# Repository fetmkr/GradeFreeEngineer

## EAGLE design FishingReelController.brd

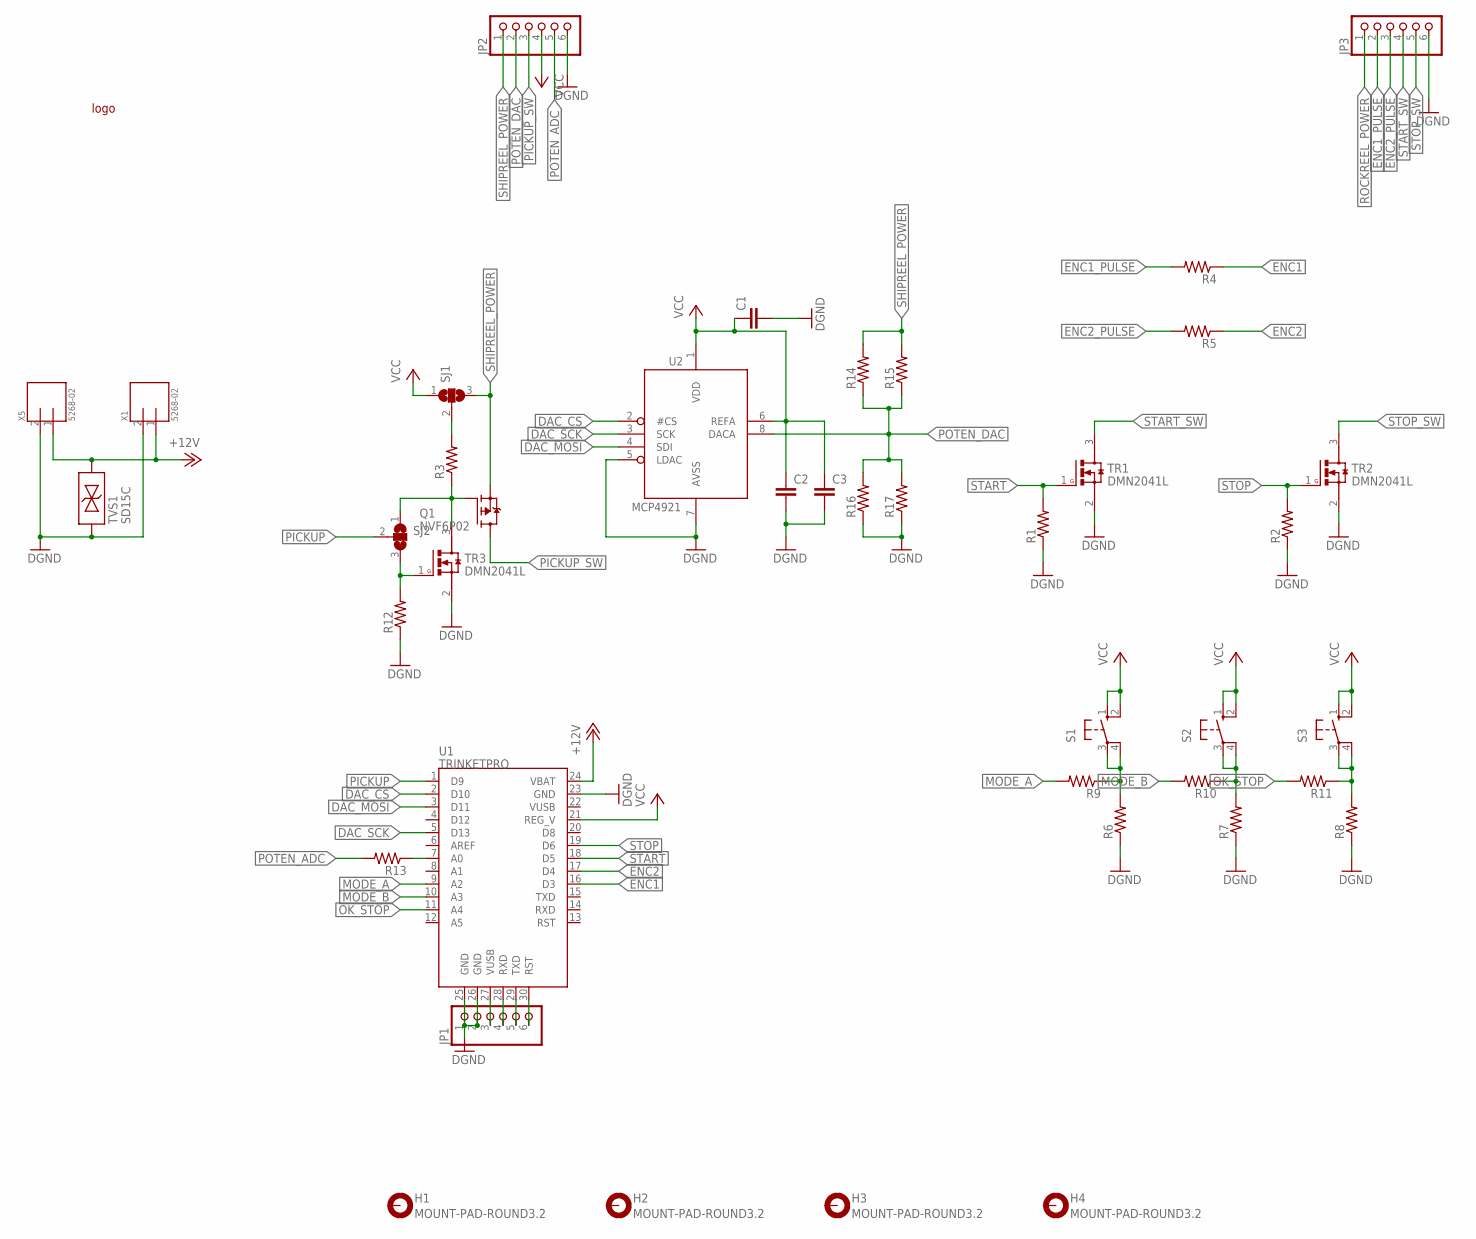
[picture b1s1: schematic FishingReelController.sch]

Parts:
C1, C2, C3: C0603(1608)
H1, H2, H3, H4: MOUNT-PAD-ROUND3.2; 3,2-PAD
JP1, JP2, JP3: PINHD-1X6CB; 1X06-CLEANBIG
LOGO1: GRADEFREELOGO-20
Q1: NVF6P02; SOT223
R1, R2, R3, R4, R5, R6, R7, R8, R9, R10, R11, R12, R13, R14, R15, R16, R17: R0603(1608)
S1, S2, S3: 40-XX; B3F-40XX
SJ1, SJ2: SJ2W; SJ_2
TR1, TR2, TR3: DMN2041L; SOT23
TVS1: SD15C; SOD-323-NOPOL
U1: TRINKETPRO
U2: MCP4921; DIL08
X1, X5: 5268-02; 5628-02

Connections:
+12V: TVS1.2, U1.24 (VBAT), X1.1, X5.1
DAC_CS: U1.2 (D10), U2.2 (#CS)
DAC_MOSI: U1.3 (D11), U2.4 (SDI)
DAC_SCK: U1.5 (D13), U2.3 (SCK)
DGND: C1.2, C2.2, C3.2, JP1.1, JP1.2, JP2.6, JP3.6, R1.1, R2.1, R6.1, R7.1, R8.1, R12.1, R16.1, R17.1, TR1.2 (S), TR2.2 (S), TR3.2 (S), TVS1.1, U1.23 (GND), U1.25 (GND), U1.26 (GND), U2.5 (LDAC), U2.7 (AVSS), X1.2, X5.2
ENC1: R4.1, U1.16 (D3)
ENC1_PULSE: JP3.2, R4.2
ENC2: R5.1, U1.17 (D4)
ENC2_PULSE: JP3.3, R5.2
MODE_A: R9.2, U1.9 (A2)
MODE_B: R10.2, U1.10 (A3)
unnamed: R12.2, SJ2.3, TR3.1 (G)
unnamed: JP1.3, U1.27 (VUSB)
unnamed: JP1.4, U1.28 (RXD)
unnamed: JP1.5, U1.29 (TXD)
unnamed: JP1.6, U1.30 (RST)
unnamed: Q1.1 (G), R3.1, SJ2.1, TR3.3 (D)
unnamed: R13.1, U1.7 (A0)
unnamed: R3.2, SJ1.2
unnamed: R6.2, R9.1, S1.3, S1.4 (P1)
unnamed: R7.2, R10.1, S2.3, S2.4 (P1)
unnamed: R8.2, R11.1, S3.3, S3.4 (P1)
OK_STOP: R11.2, U1.11 (A4)
PICKUP: SJ2.2, U1.1 (D9)
PICKUP_SW: JP2.3, Q1.2 (D), Q1.4 (D)
POTEN_ADC: JP2.5, R13.2
POTEN_DAC: JP2.2, R14.1, R15.1, R16.2, R17.2, U2.8 (DACA)
ROCKREEL_POWER: JP3.1
SHIPREEL_POWER: JP2.1, Q1.3 (S), R14.2, R15.2, SJ1.3
START: R1.2, TR1.1 (G), U1.18 (D5)
START_SW: JP3.4, TR1.3 (D)
STOP: R2.2, TR2.1 (G), U1.19 (D6)
STOP_SW: JP3.5, TR2.3 (D)
VCC: C1.1, C2.1, C3.1, JP2.4, S1.1 (S), S1.2 (S1), S2.1 (S), S2.2 (S1), S3.1 (S), S3.2 (S1), SJ1.1, U1.21 (REG_V), U2.1 (VDD), U2.6 (REFA)

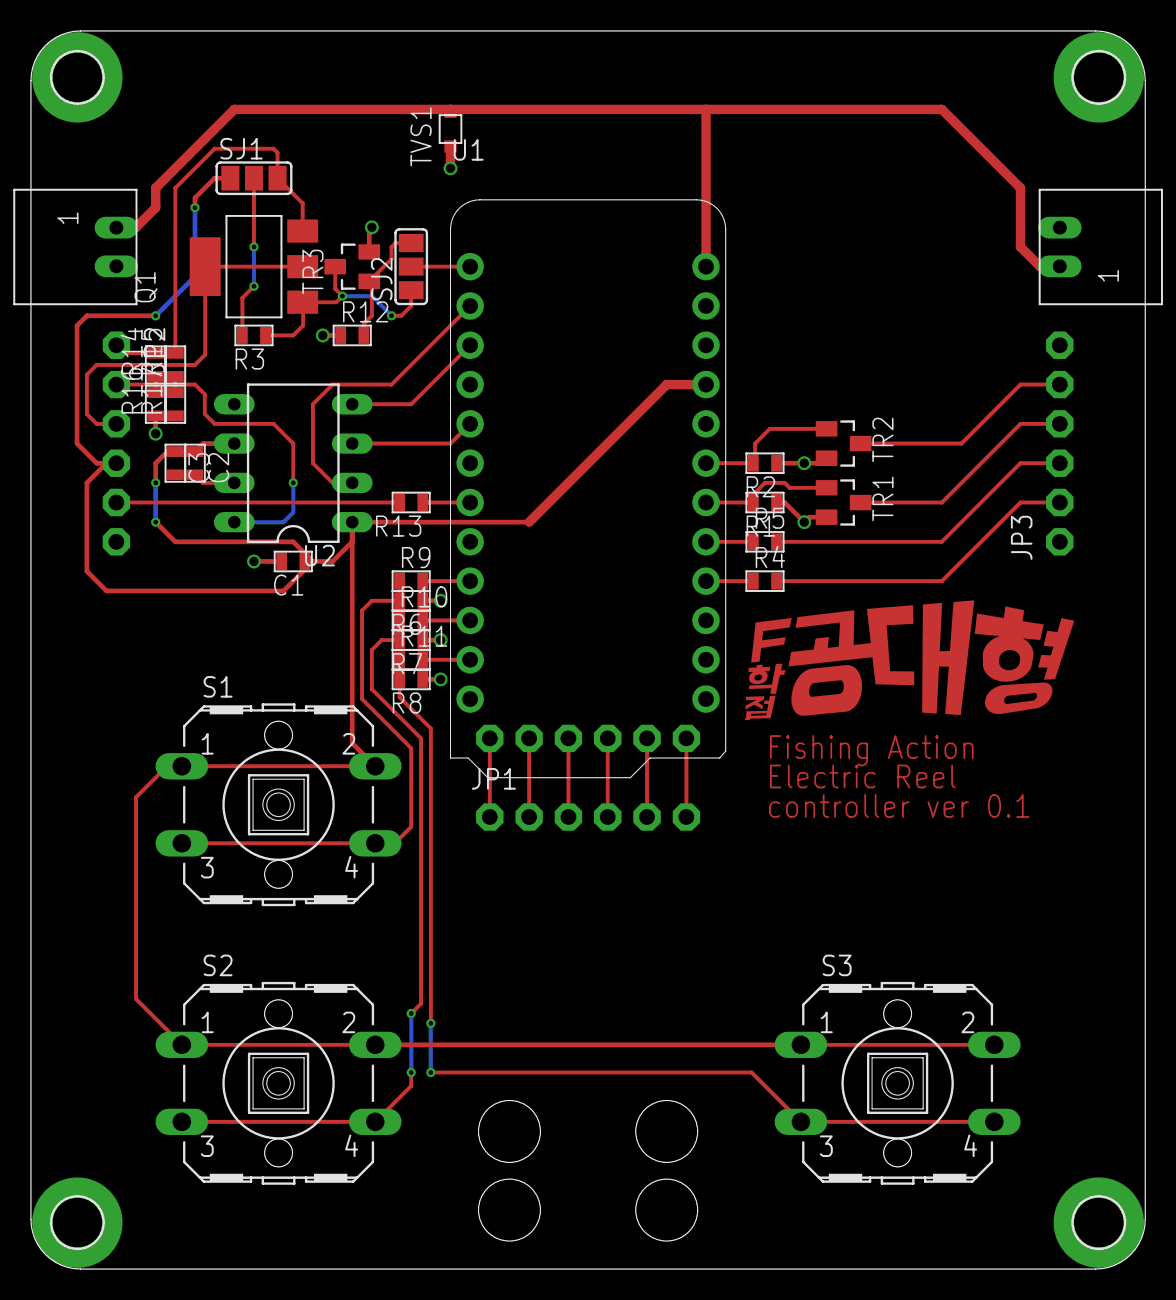
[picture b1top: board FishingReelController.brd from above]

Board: 2 copper layers, 72.0 x 80.0 mm, 42 parts (0 on the bottom side), 33 nets.

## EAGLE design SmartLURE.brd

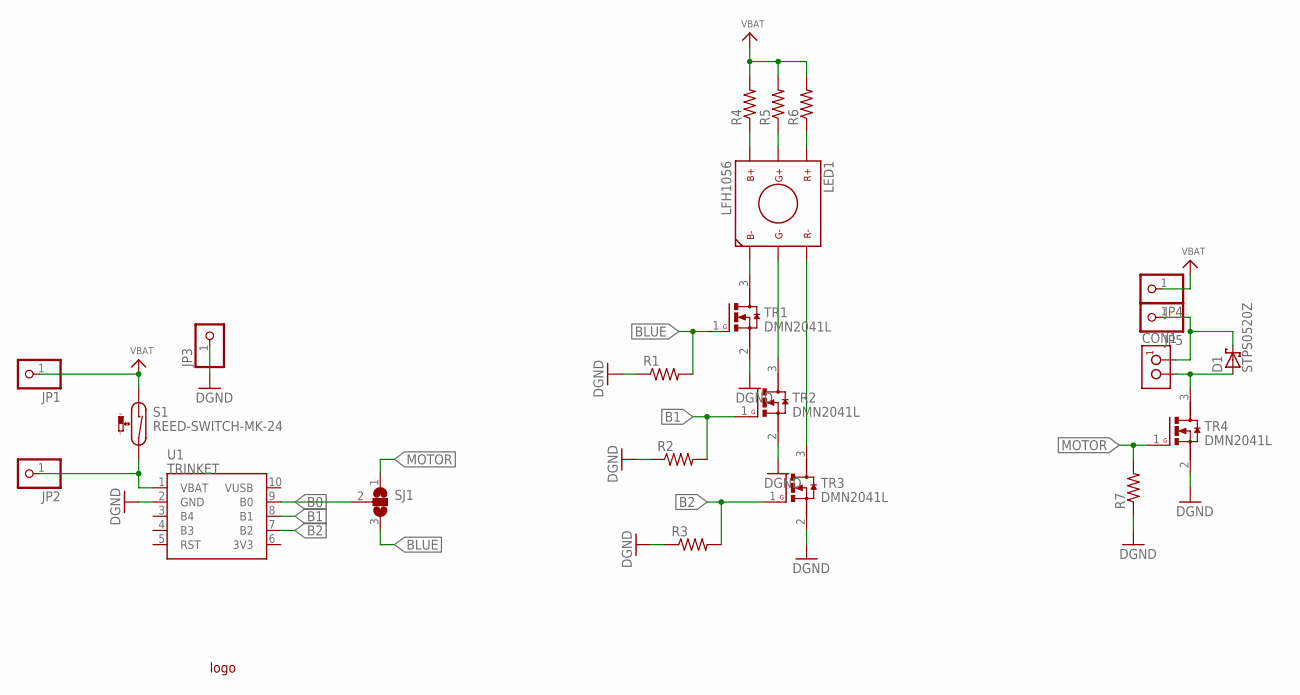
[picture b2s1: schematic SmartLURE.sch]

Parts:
CON1: PINHEADER_1.27
D1: STPS0520Z; SOD-123
JP1, JP2, JP3, JP4, JP5: PINHD-1X1CB; 1X01-CLEANBIG
LED1: LFH1056
LOGO1: GRADEFREELOGO-10
R1, R2, R3, R4, R5, R6, R7: R0603(1608)
S1: REED-SWITCH-MK-24; MK24
SJ1: SJ2W; SJ_2
TR1, TR2, TR3, TR4: DMN2041L; SOT23
U1: TRINKET

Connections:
B0: SJ1.2, U1.9 (B0)
B1: R2.2, TR2.1 (G), U1.8 (B1)
B2: R3.2, TR3.1 (G), U1.7 (B2)
BLUE: R1.2, SJ1.3, TR1.1 (G)
DGND: JP3.1, R1.1, R2.1, R3.1, R7.1, TR1.2 (S), TR2.2 (S), TR3.2 (S), TR4.2 (S), U1.2 (GND)
MOTOR: R7.2, SJ1.1, TR4.1 (G)
unnamed: LED1.B+, R4.1
unnamed: LED1.G+, R5.1
unnamed: LED1.R+, R6.1
unnamed: LED1.B-, TR1.3 (D)
unnamed: LED1.G-, TR2.3 (D)
unnamed: LED1.R-, TR3.3 (D)
unnamed: JP2.1, S1.2, U1.1 (VBAT)
unnamed: CON1.P$1 (1), D1.C, JP5.1
unnamed: CON1.P$2 (2), D1.A, TR4.3 (D)
VBAT: JP1.1, JP4.1, R4.2, R5.2, R6.2, S1.1

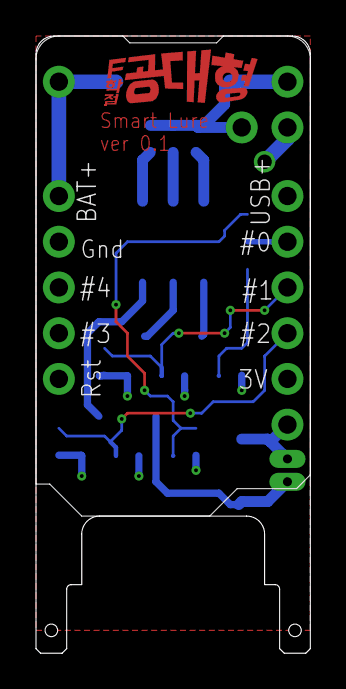
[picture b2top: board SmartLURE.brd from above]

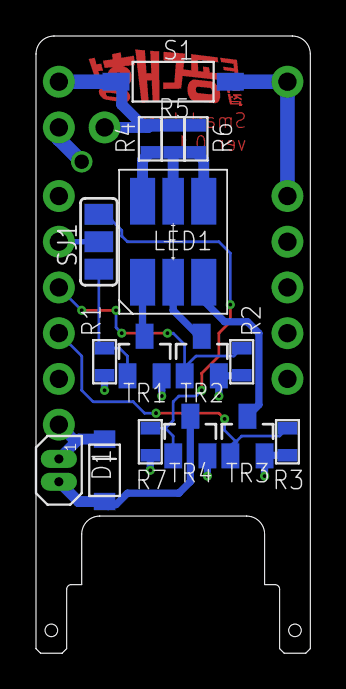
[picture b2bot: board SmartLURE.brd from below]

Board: 2 copper layers, 15.2 x 34.3 mm, 23 parts (21 on the bottom side), 16 nets.

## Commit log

2016-08-26 :neckbeard: Added .gitattributes
2016-08-26 first backup
2016-08-27 fising reel added
2016-08-27 backup
2016-08-27 gerber done

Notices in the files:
parts and their libraries:
microbuilder: This work is placed in the public domain, and may be freely used for commercial and non-commercial work with the following conditions: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
